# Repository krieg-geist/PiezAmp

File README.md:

# PiezAmp

Piezos straight into pedals sound like deep fried ass, so I built this preamp. 
There's like 1000 of these circuits, but I wanted an all in one solution that you could just throw in
a noisebox and have it sound halfway decent, with some tweaks to really dial in a nice sound.

Based on Richard Mudhar's
[low-noise piezo preamp](http://www.richardmudhar.com/blog/piezo-contact-microphone-hi-z-amplifier-low-noise-version/),
doubled up and extended. 

## Features

- **1 MΩ inputs.** Piezo discs have waaaay too high impedance for line inputs.
  At 1 MΩ they keep their full thiccness (results may vary with piezo guitar pickups, 
  this is mainly designed for cheap discs).
- **Gain:** ×1 to ×11 (0 to +20.8 dB) per channel.
- **Low noise:** about −119 dBu with a 15 nF disc, inshallah.
- **Blend** between channel A and channel B.
- **Phase invert.** This might help when you have two piezos in the same box so 
  they don't phase cancel eachother out
- **Low-cut and high-cut filters** on DIP switches: ~72 Hz low-cut for rumble/boom, and a
  three-step high-cut (10.6 / 7.2 / 4.3 kHz) if it's still too harsh/tinny. All off = flat.
- **Master volume** with a 9 mm panel pot. It shoooould (?) mount in line with the output
  jack.
- **Mono output** on a TRS jack (TS or TRS lead both fine), plus optional **direct A/B
  outs** on headers J8/J9, taken before the blend. I mainly did these to use with digital
  drum triggers, so for a basic noisebox setup you can ignore them.
- **Power:** 9–18 V DC, should work with a 9v battery, or with pretty much any barreljack
  adapter you have lying around.

## How it works

- Read [Richard Mudhar's blog](http://www.richardmudhar.com/blog/piezo-contact-microphone-hi-z-amplifier-low-noise-version/) lol

## Connections

| Ref | Header / part | Pin 1 | Pin 2 | Pin 3 |
|---|---|---|---|---|
| J5 | Piezo A in | signal | GND | |
| J6 | Piezo B in | signal | GND | |
| J4 | Power in + switch | +9–18 V in | +V to board (switch across 1–2) | GND |
| RV5 | Master volume (9 mm right-angle pot) | GND | wiper (out) | top |
| J3 | Output, 6.35 mm TRS | tip = out | ring = not connected | sleeve = GND |
| J8 | Direct out A (optional) | signal | GND | |
| J9 | Direct out B (optional) | signal | GND | |

The inputs are 2-pin headers. You can put jacks on em or just wire the piezos directly
to the inputs. Polarity shouldn't matter.

If you don't want an on/off switch, put a jumper cap across J4 pins 1–2.

## Controls

| Control | Function |
|---|---|
| Gain A / gain B | ×1 - ×11 gain, CW = more gain |
| Blend | A <-> B |
| Master volume | CW = louder |

**DIP switch SW2** (fine to flip with the power on):

| Pos | Function |
|---|---|
| 1 | Channel B polarity invert |
| 2 | Low-cut (high-pass) ~72 Hz when **OFF**; ON = flat |
| 3 | High-cut (low-pass), 10.6 kHz |
| 4 | High-cut (low-pass), 7.2 kHz |

3 and 4 together give 4.3 kHz, so the high-cut has four settings: off, 10.6, 7.2, 4.3 kHz.

Signal path: blend -> low-cut -> high-cut -> gate -> volume -> tip.

**Direct outs (J8/J9):** A and B straight off the preamps, after the gain trims
(and B's polarity switch) but before blend, filters, gate and volume. Wire them to
jacks if you want separate channels.

**Setting up:** Make a loud noise, and raise each
gain until the output is just below clipping. Try flip DIP 1: whichever setting sounds nicer is
right. Then set the blend, the filters and the master to taste.

## Customisation

- **Trimmers to panel pots.** Any trimmer (RV1–RV3) can be replaced by a panel
  pot wired to its three pads:
  - Pot lug 1 -> pad 1, wiper -> pad 2, lug 3 -> pad 3. The board already ties
    pads 2 and 3 where the circuit needs a variable resistor.
  - Use the same resistance value as the trimmer. The exception is RV3, where
    anything from 5k to 10k works.
- **Jumpering trimmers to fixed settings.** Leave the trimmer out and link or
  fit parts instead:
  - **Gain, fixed:** link pads 1–2 for minimum gain (×1). For any other fixed
    gain, fit a resistor R across pads 1–2: gain = 1 + R / 2.5 kΩ (10k ≈ ×5).
    Never link only pads 2–3: that leaves the stage with no DC feedback.
  - **Blend, fixed:** link pads 2–1 for A only, or pads 2–3 for B only. For an
    equal mix, fit two equal resistors (about 2.2k), one from pad 1 to pad 2
    and one from pad 3 to pad 2.
  - **Master volume:** RV5's holes also take a 1×3 pin header for an off-board
    pot. For fixed full volume, link pads 2–3.
- **Different filter corners:** low-cut fc = 1 / (2π · R43 · C43), so 22k/100n = 72 Hz
  (15k ≈ 110 Hz, 33k ≈ 50 Hz). High-cut fc = 1 / (2π · R40 · C40), so 10k/1.5n = 10.6 kHz.
  C44 sits in parallel with C40 (2.2n = 7.2 kHz, both = 4.3 kHz). For a brighter set use
  C40 1n / C44 1.5n (16 / 10.6 / 6.4 kHz). Keep C40, C43 and C44 C0G.
- **More headroom:** run it on 18 V. Shouldn't catch fire.

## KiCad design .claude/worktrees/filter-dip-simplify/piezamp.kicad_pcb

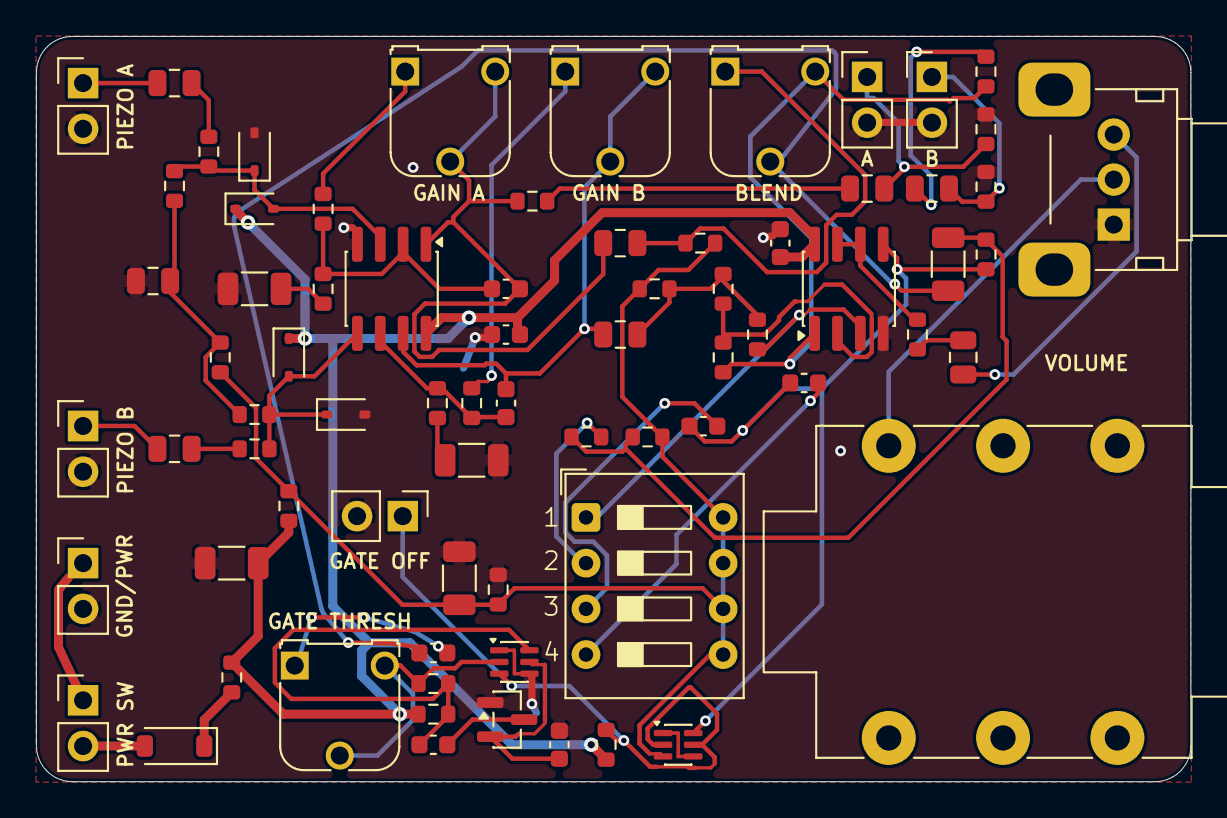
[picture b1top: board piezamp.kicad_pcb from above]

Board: 2 copper layers, 64.1 x 41.4 mm, 74 parts (0 on the bottom side), 47 nets.

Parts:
C10, C20: 1uF; C_0805_2012Metric
C11, C21, C30, C33: 22uf; C_1206_3216Metric
C12, C22: 100pf; C_0603_1608Metric
C13, C23, C34, C41, C42, C45: 10uF; C_0805_2012Metric
C31, C32, C50, C51: 100nF; C_0603_1608Metric
C40: 1.5nF C0G; C_0603_1608Metric
C43: 100nF C0G; C_1206_3216Metric
C44: 2.2nF C0G; C_0603_1608Metric
C52: 220nF; C_0603_1608Metric
D1: 1N5819WS; D_SOD-123
D10, D11, D20, D21: 1N4148WS; D_SOD-323
D50: BAV99; SOT-23
J3: Output (TRS); Jack_6.35mm_Neutrik_NMJ6HCD2_Horizontal
J4: Power_Conn; PinHeader_1x02_P2.54mm_Vertical
J5: Piezo A; PinHeader_1x02_P2.54mm_Vertical
J6: Piezo B; PinHeader_1x02_P2.54mm_Vertical
J7: Gate off; PinHeader_1x02_P2.54mm_Vertical
J8: Out A; PinHeader_1x02_P2.54mm_Vertical
J9: Out B; PinHeader_1x02_P2.54mm_Vertical
Q50: 2N7002DW; SOT-363_SC-70-6
Q51: MMDT3904; SOT-363_SC-70-6
R10, R20: 470R; R_0603_1608Metric
R11, R21, R50: 1M; R_0603_1608Metric
R12, R22: 1k; R_0603_1608Metric
R13, R23: 0R; R_0603_1608Metric
R14, R24, R46, R47: 100k; R_0603_1608Metric
R25, R26, R27, R31, R32, R40: 10k; R_0603_1608Metric
R30: 10R; R_0603_1608Metric
R33: 47k; R_0603_1608Metric
R41, R42, R45: 100R; R_0603_1608Metric
R43: 22k; R_0603_1608Metric
R44, R52: 470k; R_0603_1608Metric
R51: 4.7k; R_0603_1608Metric
RV1, RV2: 10k; Potentiometer_Runtron_RM-065_Vertical
RV3: 5k; Potentiometer_Runtron_RM-065_Vertical
RV5: 10k log; Potentiometer_Alps_RK09K_Single_Horizontal
RV6: 1M; Potentiometer_Runtron_RM-065_Vertical
SW1: Power; PinHeader_1x02_P2.54mm_Vertical
SW2: Polarity / Filter; SW_DIP_SPSTx04_Slide_9.78x12.34mm_W7.62mm_P2.54mm
U1, U2: NE5532DR; SOIC-8_3.9x4.9mm_P1.27mm

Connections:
/A_OUT: C12.2, C13.2, R45.1, RV1.2, RV1.3, U1.1
/BLEND: C43.1, C50.1, RV3.2
/B_AC: C42.2, J9.1, R47.1
/GATE: J7.1, Q50.2, Q50.5, Q51.3, R52.2
/HPF_SW: R43.2, SW2.2
/LPF: C40.1, C44.1, Q50.6, R40.2, U2.5 (+)
/LPF2_SW: C44.2, SW2.4
/LPF_SW: C40.2, SW2.3
/POL_P: R27.2, SW2.1, U2.3 (+)
/VREF: C33.1, Q50.3, R14.2, R24.2, R31.2, R32.1, R33.1, R44.2, SW2.5, SW2.6, SW2.7, SW2.8
/VREF_IN: C34.1, R11.2, R21.2, R33.2
GND: C11.2, C21.2, C30.2, C31.2, C32.2, C33.2, C34.2, C52.2, D11.2 (A), D21.2 (A), D50.1, J3.S, J4.2, J5.2, J6.2, J7.2, J8.2, J9.2, Q51.1, Q51.4, R32.2, R46.2, R47.2, RV5.1, U1.4 (V-), U2.4 (V-)
unnamed: C10.2, R10.1
unnamed: C11.1, R12.2
unnamed: C13.1, R14.1, RV3.1
unnamed: C20.2, R20.1
unnamed: C21.1, R22.2
unnamed: C22.2, C23.2, RV2.2, RV2.3, U1.7
unnamed: C23.1, R24.1, R25.1, R27.1
unnamed: C41.1, R41.2
unnamed: C41.2, RV5.3
unnamed: C42.1, R42.2
unnamed: C43.2, R40.1, R43.1, R44.1
unnamed: C45.1, R45.2
unnamed: C50.2, RV6.1
unnamed: C51.2, D50.3
unnamed: D1.2 (A), SW1.2 (B)
unnamed: D1.1 (K), R30.1
unnamed: D10.2 (A), D11.1 (K), R10.2, R11.1, U1.3 (+)
unnamed: D20.2 (A), D21.1 (K), R20.2, R21.1, U1.5 (+)
unnamed: C52.1, D50.2, Q51.5
unnamed: J3.T, RV5.2
unnamed: J4.1, SW1.1 (A)
unnamed: C10.1, J5.1
unnamed: C20.1, J6.1
unnamed: C45.2, J8.1, R46.1
unnamed: Q50.1, Q50.4
unnamed: Q51.2, R50.1, RV6.2, RV6.3
unnamed: C51.1, Q51.6, R50.2, R51.2
unnamed: R13.2, RV1.1
unnamed: R23.2, RV2.1
unnamed: R26.2, R42.1, RV3.3, U2.1
unnamed: C12.1, R12.1, R13.1, U1.2 (-)
unnamed: C22.1, R22.1, R23.1, U1.6 (-)
unnamed: R25.2, R26.1, U2.2 (-)
unnamed: R41.1, U2.6 (-), U2.7
VCC: C30.1, C31.1, C32.1, D10.1 (K), D20.1 (K), R30.2, R31.1, R51.1, R52.1, U1.8 (V+), U2.8 (V+)
